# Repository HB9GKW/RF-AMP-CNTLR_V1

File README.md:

# RF-AMP-CNTLR_V1
HB9GKW RF Amplifier Controller

Features:

* Save sequencing of: 
	- Input and output relays with handshake and adjustable delays
	- Amplifier gate enable
	- ALC blanking voltage

* Control of up to 2 power amplifier modules

* Fast analog interlocking:
	- 4x VSWR
	- 2x RF input overload
	- Overcurrent
	- 2x Temperature

* High power MOSFET high side switch with voltage/current sense to disable amplifiers drain supply

* PTT input and adjustable ALC output

* Digital monitoring interface compatible for Raspberry Pi (40 pin header):
	- Amplifier operation and fault states
	- 12 ADC channels (12bit) for voltage, current, 4x forward/reflected, 2x temperature reading

* On-board power supplies (12V, -12V, 5V, 3.3V)

* Can be powered either by mains or external 13.8V supply

* Enhanced RF relay switching speed circuitry compatible for 12V and 24V RF relays

* Radio CAT control, Band and Antenna switching and general purpose interfacing ports for I2C and SPI

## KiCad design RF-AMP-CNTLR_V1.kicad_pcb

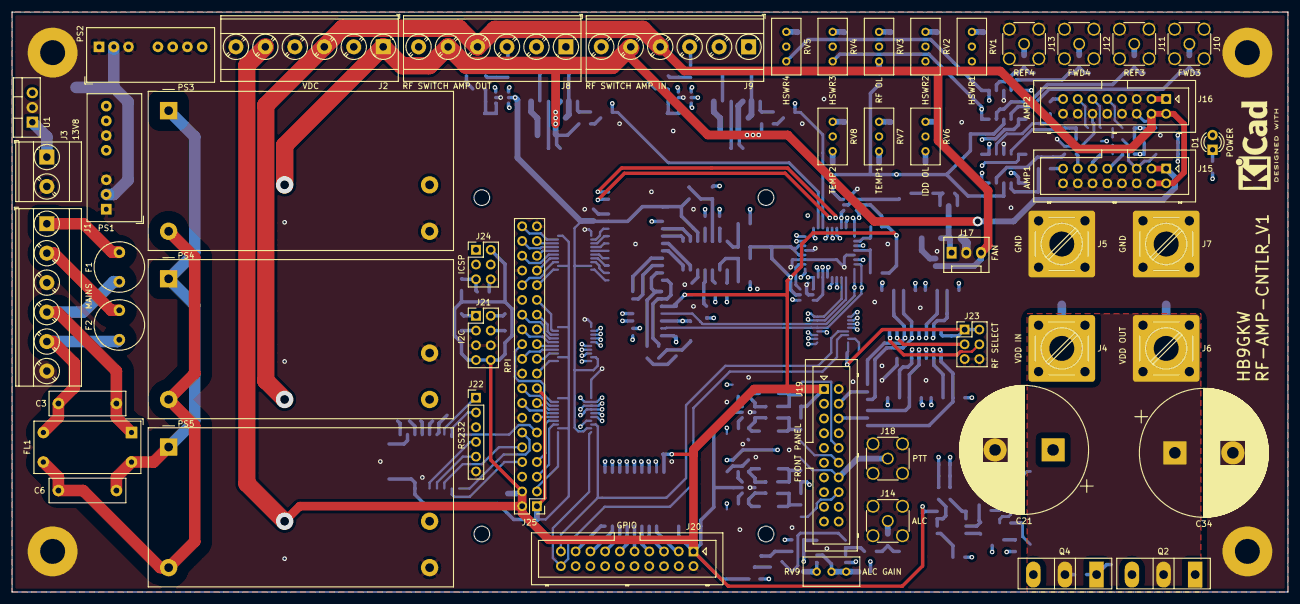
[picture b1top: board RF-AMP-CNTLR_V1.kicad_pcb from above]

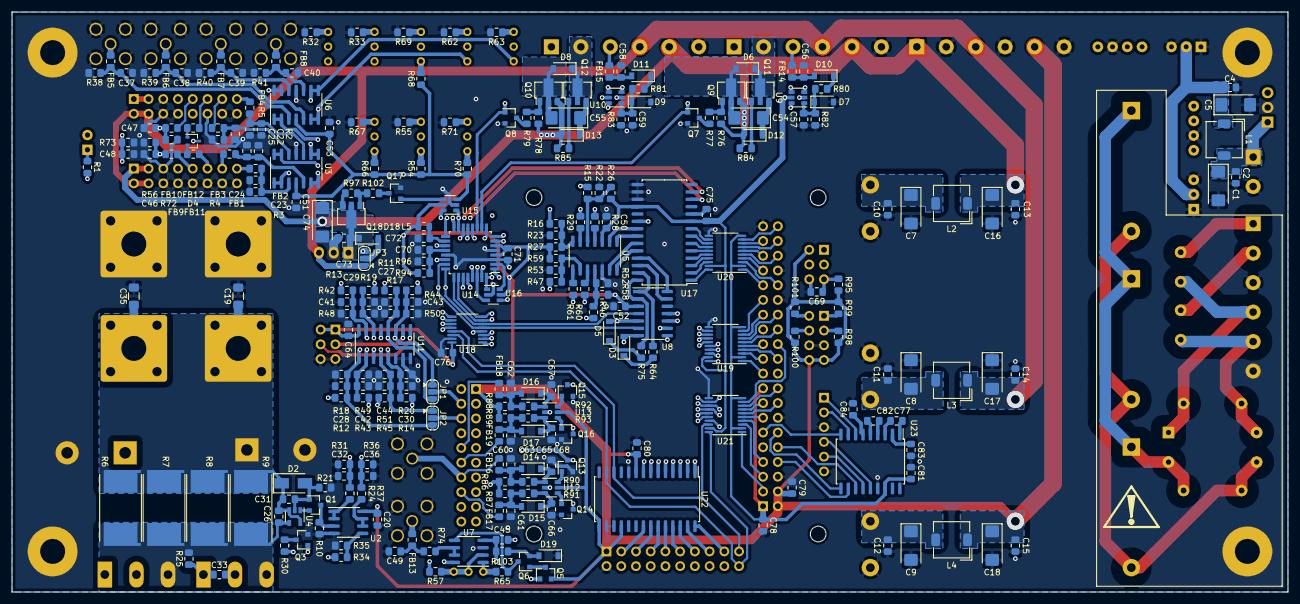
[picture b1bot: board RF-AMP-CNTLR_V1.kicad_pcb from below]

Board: 4 copper layers, 220.0 x 100.0 mm, 316 parts (266 on the bottom side), 252 nets.

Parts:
C1, C5, C7, C8, C9, C16, C17, C18, C74: 47u; CP_EIA-6032-28_Kemet-C
C2, C4, C10, C11, C12, C13, C14, C15, C20, C26, C31, C32, C33, C36, C45, C49, C50, C51, C52, C53, C64, C66, C67, C68, C70, C71, C72, C75, C76, C77, C78, C79, C80, C81, C82, C83, C84: 100n; C_0805_2012Metric_Pad1.15x1.40mm_HandSolder
C3, C6: 68n; C_Rect_L13.0mm_W4.0mm_P10.00mm_FKS3_FKP3_MKS4
C19, C35: 100n; C_1206_3216Metric_Pad1.42x1.75mm_HandSolder
C21, C34: 470u; CP_Radial_D22.0mm_P10.00mm_SnapIn
C22, C23, C24, C25, C37, C38, C39, C40, C48, C60, C61, C62, C63, C69, C73: 1n; C_0805_2012Metric_Pad1.15x1.40mm_HandSolder
C27, C28, C29, C30, C41, C42, C43, C44, C46, C47, C56, C57, C58, C59: 47n; C_0805_2012Metric_Pad1.15x1.40mm_HandSolder
C54, C55: 4u7; CP_EIA-6032-28_Kemet-C
C65: 10n; C_0805_2012Metric_Pad1.15x1.40mm_HandSolder
D1: Power; LED_D3.0mm
D2: Z1SMA33; D_SMA
D3, D5, D10, D11, D14, D15, D16, D17: 1N4148W; D_SOD-123
D4: BAT54CW; SOT-323_SC-70
D6, D8, D12, D13, D18: PMEG6010CEH; D_SOD-123
D7, D9, D19: BZT52C4V7T-7; D_SOD-123
F1, F2: 1AT; Fuse_Littelfuse_372_D8.50mm
FB1, FB2, FB3, FB4, FB5, FB6, FB7, FB8, FB9, FB10, FB11, FB12, FB13, FB14, FB15, FB16, FB17, FB18, FB19: Ferrite_Bead_Small; R_0805_2012Metric_Pad1.15x1.40mm_HandSolder
FL1: EMI_Filter_CommonMode; Choke_Schaffner_RN202-04-8.8x18.2mm
J1: VAC; TerminalBlock_Phoenix_MKDS-3-6-5.08_1x06_P5.08mm_Horizontal
J2: VDC; TerminalBlock_Phoenix_MKDS-3-6-5.08_1x06_P5.08mm_Horizontal
J3: ext_13V8; TerminalBlock_Phoenix_MKDS-3-2-5.08_1x02_P5.08mm_Horizontal
J4: VDD IN; TerminalBlock_MetzConnect_360425_1x01_Horizontal_ScrewM4.0_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
J5: VSS IN; TerminalBlock_MetzConnect_360425_1x01_Horizontal_ScrewM4.0_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
J6: VDD OUT; TerminalBlock_MetzConnect_360425_1x01_Horizontal_ScrewM4.0_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
J7: VSS OUT; TerminalBlock_MetzConnect_360425_1x01_Horizontal_ScrewM4.0_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
J8: RF SWITCH AMP OUT; TerminalBlock_Phoenix_MKDS-3-6-5.08_1x06_P5.08mm_Horizontal
J9: RF SWITCH AMP IN; TerminalBlock_Phoenix_MKDS-3-6-5.08_1x06_P5.08mm_Horizontal
J10: FWD3; SMA_Amphenol_132134_Vertical
J11: REF3; SMA_Amphenol_132134_Vertical
J12: FWD4; SMA_Amphenol_132134_Vertical
J13: REF4; SMA_Amphenol_132134_Vertical
J14: ALC; SMA_Amphenol_132134_Vertical
J15: AMP1; Multicomp_MC9A12-1634_2x08_P2.54mm_Vertical
J16: AMP2; Multicomp_MC9A12-1634_2x08_P2.54mm_Vertical
J17: FAN; FanPinHeader_1x03_P2.54mm_Vertical
J18: PTT; SMA_Amphenol_132134_Vertical
J19: FRONT PANEL; Multicomp_MC9A12-2034_2x10_P2.54mm_Vertical
J20: GPIO; Multicomp_MC9A12-2034_2x10_P2.54mm_Vertical
J21: I2C; PinHeader_2x04_P2.54mm_Vertical
J22: UART; PinHeader_1x06_P2.54mm_Vertical
J23: Conn_02x03_Odd_Even; PinHeader_2x03_P2.54mm_Vertical
J24: ICSP; PinHeader_2x03_P2.54mm_Vertical
J25: Raspberry_Pi_2_3; PinHeader_2x20_P2.54mm_Vertical
JP1, JP2, JP3: SolderJumper_3_Bridged12; SolderJumper-3_P1.3mm_Open_RoundedPad1.0x1.5mm
L1, L2, L3, L4: 10u; L_TDK_SLF6045
L5: 10u; L_0805_2012Metric
PS1: ITQ2412SA; Converter_DCDC_XP_POWER-ITXxxxxSA_THT
PS2: ITQ2405SA; Converter_DCDC_XP_POWER-ITXxxxxSA_THT
PS3, PS4: IRM-20-12; Converter_ACDC_MeanWell_IRM-20-xx_THT
PS5: IRM-20-5; Converter_ACDC_MeanWell_IRM-20-xx_THT
Q1: BC857; SOT-23
Q2, Q4: IXTH140P10T; TO-247-3_Vertical
Q3, Q6, Q7, Q8, Q13, Q14, Q15, Q16, Q17: DTC124E; SOT-23
Q5: DTA124E; SOT-23
Q9, Q10, Q11, Q12, Q18: BCX53; SOT-89-3
R1: 2k2; R_0805_2012Metric_Pad1.15x1.40mm_HandSolder
R2, R3, R4, R5, R38, R39, R40, R41, R56, R72: 100k; R_0805_2012Metric_Pad1.15x1.40mm_HandSolder
R6, R7, R8, R9: 0R015; R_Shunt_Vishay_WSR2_WSR3_KelvinConnection
R10: 68k; R_0805_2012Metric_Pad1.15x1.40mm_HandSolder
R11, R12, R13, R14, R24, R37, R42, R43, R44, R45, R74: 330; R_0805_2012Metric_Pad1.15x1.40mm_HandSolder
R15, R16, R46, R47: 8k2; R_0805_2012Metric_Pad1.15x1.40mm_HandSolder
R17, R18, R19, R20, R25, R31, R34, R36, R48, R49, R50, R51, R57, R65, R82, R83, R84, R85, R86, R87, R88, R89, R90, R91, R92, R93, R95, R98, R99, R100, R101: 10k; R_0805_2012Metric_Pad1.15x1.40mm_HandSolder
R21, R28, R29, R54, R60, R61, R66, R68, R70, R76, R78, R96, R97, R103: 4k7; R_0805_2012Metric_Pad1.15x1.40mm_HandSolder
R22, R23, R52, R53, R55, R67, R69, R71, R80, R81, R94: 1k; R_0805_2012Metric_Pad1.15x1.40mm_HandSolder
R26, R27, R30, R58, R59: 47k; R_0805_2012Metric_Pad1.15x1.40mm_HandSolder
R32, R33, R62, R63, R64, R75: 15k; R_0805_2012Metric_Pad1.15x1.40mm_HandSolder
R35: 680; R_0805_2012Metric_Pad1.15x1.40mm_HandSolder
R73: 470; R_0805_2012Metric_Pad1.15x1.40mm_HandSolder
R77, R79, R102: 110; R_0805_2012Metric_Pad1.15x1.40mm_HandSolder
RV1, RV2, RV3, RV4, RV5, RV6, RV7, RV8, RV9: 20k; Potentiometer_Bourns_3296W_Vertical
U1: L7812; TO-220-3_Vertical
U2, U7: NCS20072D; SOIC-8_3.9x4.9mm_P1.27mm
U3, U6: NCS20074D; SOIC-14_3.9x8.7mm_P1.27mm
U4: INA138; SOT-23-5
U5, U8: LM339; SOIC-14_3.9x8.7mm_P1.27mm
U9, U10: 74LVC2G17; SOT-23-6
U11: CD4052B; SOIC-16_3.9x9.9mm_P1.27mm
U12, U13: 74LVC2G14; SOT-23-6
U14: ATmega8-16AU; TQFP-32_7x7mm_P0.8mm
U15, U16: SN74LVC1G11DBVR; SOT-23-6
U17, U22: MCP23017_SO; SOIC-28W_7.5x17.9mm_P1.27mm
U18: MAX11616; QSOP-16_3.9x4.9mm_P0.635mm
U19, U20, U21: TXS0108EPW; TSSOP-20_4.4x6.5mm_P0.65mm
U23: MAX3232; SOIC-18W_7.5x11.6mm_P1.27mm

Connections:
+3V3: C78.1, C81.1, J25.1, J25.17, U19.2, U19.10, U20.2, U20.10, U21.2, U21.10, U23.16
+5V: C15.1, C18.1, C20.1, C50.1, C51.1, C52.1, C53.1, C64.1, C71.1, C75.1, C76.1, C79.1, C80.1, J2.5, J19.1, J20.1, J21.7, J21.8, J23.1, J23.2, J24.2, J25.2, J25.4, L4.1, L5.2, Q5.2, R26.2, R27.2, R54.1, R58.2, R59.2, R66.1, R68.1, R70.1, R86.1, R87.1, R88.1, R89.1, R94.2, R95.1, R98.2, R99.2, R100.2, R101.2, U2.8, U3.4, U5.3, U6.4, U8.3, U9.5, U10.5, U11.16, U12.5, U13.5, U14.4, U14.6, U15.3, U15.5, U16.5, U17.9, U17.18, U18.16, U19.19, U20.19, U21.19, U22.9, U22.15, U22.18
+12V: C13.1, C16.1, C45.1, C74.1, D1.2, D12.2, D13.2, J2.1, J8.5, J9.5, J15.1, J15.3, J16.1, J16.3, L2.1, Q9.3, Q10.3, Q18.3, R76.2, R78.2, R84.2, R85.2, R97.2, U7.8
-12V: C14.1, C17.2, C45.2, J2.3, J8.4, J9.4, J15.2, J15.4, J16.2, J16.4, J17.3, JP3.1, L3.1, R1.2, R103.2, U7.4
/+5V_: C9.1, C12.1, L4.2, PS2.6, PS5.4
/+12V_: C7.1, C10.1, L2.2, PS3.4, U1.3
/-12V_: C8.2, C11.1, L3.2, PS1.7, PS4.3
/CONTROLLER/DISPLAY: Q16.3, U14.14, U19.13
/CONTROLLER/DISPLAY_: FB19.2, J19.12
/CONTROLLER/DISPLAY_LV: J25.27, U19.8
/CONTROLLER/FAN+: C73.1, D18.1, J17.1, Q18.2
/CONTROLLER/FAULT: J19.19, U14.8, U21.17
/CONTROLLER/FAULT_LV: J25.7, U21.4
/CONTROLLER/GATE_ALC_EN_LV: J25.16, U21.6
/CONTROLLER/GPA0: J20.3, U22.21
/CONTROLLER/GPA1: J20.5, U22.22
/CONTROLLER/GPA2: J20.7, U22.23
/CONTROLLER/GPA3: J20.9, U22.24
/CONTROLLER/GPA4: J20.11, U22.25
/CONTROLLER/GPA5: J20.13, U22.26
/CONTROLLER/GPA6: J20.15, U22.27
/CONTROLLER/GPA7: J20.17, U22.28
/CONTROLLER/GPB0: J20.18, U22.1
/CONTROLLER/GPB1: J20.16, U22.2
/CONTROLLER/GPB2: J20.14, U22.3
/CONTROLLER/GPB3: J20.12, U22.4
/CONTROLLER/GPB4: J20.10, U22.5
/CONTROLLER/GPB5: J20.8, U22.6
/CONTROLLER/GPB6: J20.6, U22.7
/CONTROLLER/GPB7: J20.4, U22.8
/CONTROLLER/HSWR1: U17.1, U20.20
/CONTROLLER/HSWR1_LV: J25.31, U20.1
/CONTROLLER/HSWR2: U17.2, U20.18
/CONTROLLER/HSWR2_LV: J25.32, U20.3
/CONTROLLER/HSWR3: U17.3, U20.17
/CONTROLLER/HSWR3_LV: J25.33, U20.4
/CONTROLLER/HSWR4: U17.4, U20.16
/CONTROLLER/IDD_OL: U17.6, U20.14
/CONTROLLER/IDD_OL_LV: J25.38, U20.7
/CONTROLLER/ILK: U14.32, U16.1, U17.20
/CONTROLLER/ILK_HSWR1: U5.2, U17.21
/CONTROLLER/ILK_HSWR2: U5.1, U17.22
/CONTROLLER/ILK_HSWR3: U5.13, U17.23
/CONTROLLER/ILK_HSWR4: U5.14, U17.24
/CONTROLLER/ILK_IDD_OL: U8.13, U17.26
/CONTROLLER/ILK_RF_OL: U8.14, U17.25
/CONTROLLER/ILK_TEMP1: R64.2, U8.1, U17.27
/CONTROLLER/ILK_TEMP2: R75.2, U8.2, U17.28
/CONTROLLER/MISO_RF_INHIBIT: J24.1, U14.16, U19.18
/CONTROLLER/MISO_RF_INHIBIT_LV: J25.21, U19.3
/CONTROLLER/MOSI_FAN: J24.4, U14.15, U15.1, U19.20
/CONTROLLER/MOSI_FAN_LV: J25.19, U19.1
/CONTROLLER/ON_AIR: J19.17, U14.7, U21.16
/CONTROLLER/ON_AIR_LV: J25.13, U21.5
/CONTROLLER/OPR: Q14.3, U14.12, U19.15
/CONTROLLER/OPR_: FB17.2, J19.16
/CONTROLLER/OPR_LV: J25.26, U19.6
/CONTROLLER/PTT: Q13.3, U14.1, U19.14
/CONTROLLER/PTT_: FB16.2, J18.1, J19.14
/CONTROLLER/PTT_LV: J25.28, U19.7
/CONTROLLER/RESET_ILK: Q15.3, U14.13, U19.12
/CONTROLLER/RESET_ILK_: FB18.2, J19.10
/CONTROLLER/RESET_ILK_LV: J25.29, U19.9
/CONTROLLER/RESET_ISP: C69.1, J24.5, R95.2, U14.29, U15.6, U19.17
/CONTROLLER/RESET_ISP_LV: J25.22, U19.4
/CONTROLLER/RF_OL: U17.5, U20.15
/CONTROLLER/RF_OL_LV: J25.35, U20.6
/CONTROLLER/RF_SW1_ON_LV: J25.18, U21.8
/CONTROLLER/RF_SW2_ON_LV: J25.15, U21.7
/CONTROLLER/RXD0: J25.10, U23.12
/CONTROLLER/RXD0_RS: J22.5, U23.13
/CONTROLLER/RXD1: J25.11, U23.9
/CONTROLLER/RXD1_RS: J22.2, U23.8
/CONTROLLER/SCK_SOFT_ILK: J24.3, U14.17, U19.16
/CONTROLLER/SCK_SOFT_ILK_LV: J25.23, U19.5
/CONTROLLER/SCL_PI_HV: J20.19, J21.4, R100.1, U18.13, U21.18, U22.12
/CONTROLLER/SCL_PI_LV: J25.5, U21.3
/CONTROLLER/SDA_PI_HV: J20.20, J21.2, R101.1, U18.14, U21.20, U22.13
/CONTROLLER/SDA_PI_LV: J25.3, U21.1
/CONTROLLER/SELA: J23.3, U11.10
/CONTROLLER/SELB: J23.4, U11.9
/CONTROLLER/TEMP: U17.8, U20.12
/CONTROLLER/TEMP_LV: J25.40, U20.9
/CONTROLLER/TXD0: J25.8, U23.11
/CONTROLLER/TXD0_RS: J22.4, U23.14
/CONTROLLER/TXD1: J25.12, U23.10
/CONTROLLER/TXD1_RS: J22.1, U23.7
/CONTROLLER/UNBAL_LV: J25.36, U20.5
/CONTROLLER/VDD_EN_LV: J25.24, U21.9
/CONTROLLER/VDD_LIM: U17.7, U20.13
/CONTROLLER/VDD_LIM_LV: J25.37, U20.8
/FRONTEND/ALC: FB13.1, J14.1
/FRONTEND/FWD1: FB1.2, J15.13
/FRONTEND/FWD2: FB3.2, J16.13
/FRONTEND/FWD3: FB5.2, J10.1
/FRONTEND/FWD4: FB7.2, J12.1
/FRONTEND/REF1: FB2.2, J15.15
/FRONTEND/REF2: FB4.2, J16.15
/FRONTEND/REF3: FB6.2, J11.1
/FRONTEND/REF4: FB8.2, J13.1
/FRONTEND/RF_OL1: FB11.2, J15.11
/FRONTEND/RF_OL2: FB12.2, J16.11
/FRONTEND/RF_SW1: D6.1, J8.2, Q11.2
/FRONTEND/RF_SW1_EN_: J8.1, U9.4
/FRONTEND/RF_SW1_ON_: FB14.1, J8.3
/FRONTEND/RF_SW2: D8.1, J9.2, Q12.2
/FRONTEND/RF_SW2_EN_: J9.1, U10.4
/FRONTEND/RF_SW2_ON_: FB15.1, J9.3
/FRONTEND/TEMP1: FB9.2, J15.9
/FRONTEND/TEMP2: FB10.2, J16.9
/FRONTEND/VDD_IN: C19.1, C21.1, C26.2, C31.1, D2.1, J4.1, R6.2, R7.2, R8.2, R9.2, U4.3, U4.5
/FRONTEND/VDD_OUT: C33.2, C34.1, C35.1, J6.1, Q2.2, Q4.2, R34.1
/FWD1_MON: C27.1, JP1.3, R11.2, R17.2, U11.12, U18.9
/FWD2_MON: C29.1, R13.2, R19.2, U11.14, U18.11
/FWD3_MON: C41.1, R42.2, R48.2, U11.15, U18.4
/FWD4_MON: C43.1, JP1.1, R44.2, R50.2, U11.11, U18.2
/GATE_ALC_EN: J15.7, J16.7, J19.15, Q5.1, U16.4, U21.15
/IDD_MON: C32.1, J19.3, R24.1, R31.2, U8.10, U14.26, U18.8
/REF1_MON: C28.1, JP2.3, R12.2, R18.2, U11.1, U18.10
/REF2_MON: C30.1, R14.2, R20.2, U11.5, U18.12
/REF3_MON: C42.1, R43.2, R49.2, U11.2, U18.3
/REF4_MON: C44.1, JP2.1, R45.2, R51.2, U11.4, U18.1
/RF_SW1_EN: Q7.1, U9.3, U14.10
/RF_SW1_ON: J19.11, U9.6, U14.30, U16.3, U21.13
/RF_SW2_EN: Q8.1, U10.3, U14.11
/RF_SW2_ON: J19.13, U10.6, U14.31, U21.14
/SCL: J19.20, J21.3, R98.1, U14.28, U17.12
/SDA: J19.18, J21.1, R99.1, U14.27, U17.13
/TEMP1_MON: C46.1, FB9.1, J19.7, R56.1, U8.6, U14.23, U18.5
/TEMP2_MON: C47.1, FB10.1, J19.9, R72.1, U8.4, U14.24, U18.6
/VDD_EN: J19.8, Q3.1, U14.9, U21.12
/VDD_MON: C36.1, J19.5, R36.2, R37.2, U14.25, U18.7
Earth: C1.2, C2.2, C4.2, C5.2, C7.2, C8.1, C9.2, C10.2, C11.2, C12.2, C13.2, C14.2, C15.2, C16.2, C17.1, C18.2, C19.2, C20.2, C21.2, C22.2, C23.2, C24.2, C25.2, C27.2, C28.2, C29.2, C30.2, C32.2, C34.2, C35.2, C36.2, C37.2, C38.2, C39.2, C40.2, C41.2, C42.2, C43.2, C44.2, C46.2, C47.2, C48.2, C49.2, C50.2, C51.2, C52.2, C53.2, C56.2, C57.2, C58.2, C59.2, C60.2, C61.2, C62.2, C63.2, C64.2, C65.2, C66.2, C67.2, C68.2, C69.2, C70.2, C71.2, C72.2, C73.2, C74.2, C75.2, C76.2, C78.2, C79.2, C80.2, C81.2, C83.2, C84.2, D7.2, D9.2, D19.1, J1.3, J1.6, J2.2, J2.4, J2.6, J3.2, J5.1, J7.1, J8.6, J9.6, J10.2, J11.2, J12.2, J13.2, J14.2, J15.5, J15.6, J15.8, J15.10, J15.12, J15.14, J15.16, J16.5, J16.6, J16.8, J16.10, J16.12, J16.14, J16.16, J17.2, J18.2, J19.2, J20.2, J21.5, J21.6, J22.3, J22.6, J23.5, J23.6, J24.6, J25.6, J25.9, J25.14, J25.20, J25.25, J25.30, J25.34, J25.39, JP3.3, PS1.1, PS1.3, PS1.6, PS2.1, PS2.3, PS2.7, PS3.3, PS4.4, PS5.3, Q3.2, Q7.2, Q8.2, Q13.2, Q14.2, Q15.2, Q16.2, Q17.2, R2.2, R3.2, R4.2, R5.2, R10.2, R17.1, R18.1, R19.1, R20.1, R21.2, R22.2, R23.2, R31.1, R32.2, R33.2, R35.2, R36.1, R38.2, R39.2, R40.2, R41.2, R48.1, R49.1, R50.1, R51.1, R52.2, R53.2, R55.2, R56.2, R62.2, R63.2, R67.2, R69.2, R71.2, R72.2, R73.2, R82.2, R83.2, R96.2, U1.2, U2.4, U3.11, U5.12, U6.11, U7.3, U8.12, U9.2, U10.2, U11.6, U11.7, U11.8, U12.2, U13.2, U14.3, U14.5, U14.21, U15.2, U16.2, U17.10, U17.15, U17.16, U17.17, U18.15, U19.11, U20.11, U21.11, U22.10, U22.16, U22.17, U23.15
FWD: J19.4, JP1.2, R57.2
unnamed: C1.1, C2.1, J3.1, L1.2, U1.1
unnamed: C3.1, F1.1, FL1.1, J1.4
unnamed: C3.2, F2.1, FL1.3, J1.5
unnamed: C4.1, C5.1, L1.1, PS1.2, PS2.2
unnamed: C6.1, FL1.2, PS3.1, PS4.1, PS5.1
unnamed: C6.2, FL1.4, PS3.2, PS4.2, PS5.2
unnamed: C22.1, FB1.1, R2.1, U3.5
unnamed: C23.1, FB2.1, R3.1, U3.3
unnamed: C24.1, FB3.1, R4.1, U3.12
unnamed: C25.1, FB4.1, R5.1, U3.10
unnamed: C26.1, Q2.3, Q4.3, R6.1, R7.1, R8.1, R9.1, R25.2, U4.4
unnamed: C31.2, D2.2, Q1.1, R21.1, U4.2
unnamed: C33.1, Q2.1, Q4.1, R25.1, R30.2
unnamed: C37.1, FB5.1, R38.1, U6.3
unnamed: C38.1, FB6.1, R39.1, U6.5
unnamed: C39.1, FB7.1, R40.1, U6.12
unnamed: C40.1, FB8.1, R41.1, U6.10
unnamed: C48.1, D4.3, R73.1, U8.8
unnamed: C49.1, FB13.2, R74.1
unnamed: C54.1, D12.1, Q11.3
unnamed: C54.2, D6.2, Q9.2
unnamed: C55.1, D13.1, Q12.3
unnamed: C55.2, D8.2, Q10.2
unnamed: C56.1, D10.2, FB14.2
unnamed: C57.1, D7.1, R80.2, R82.1, U9.1
unnamed: C58.1, D11.2, FB15.2
unnamed: C59.1, D9.1, R81.2, R83.1, U10.1
unnamed: C60.1, D14.2, FB16.1, R86.2, R90.2
unnamed: C61.1, D15.2, FB17.1, R87.2, R91.2
unnamed: C62.1, D16.2, FB18.1, R88.2, R92.2
unnamed: C63.1, D17.2, FB19.1, R89.2, R93.2
unnamed: C65.1, D14.1, R90.1, U12.1
unnamed: C66.1, D15.1, R91.1, U12.3
unnamed: C67.1, D16.1, R92.1, U13.1
unnamed: C68.1, D17.1, R93.1, U13.3
unnamed: C70.1, R94.1, R96.1, U14.20
unnamed: C72.1, L5.1, U14.18
unnamed: C77.1, U23.1
unnamed: C77.2, U23.3
unnamed: C82.1, U23.4
unnamed: C82.2, U23.5
unnamed: C83.1, U23.2
unnamed: C84.1, U23.6
unnamed: D1.1, R1.1
unnamed: D3.1, R64.1
unnamed: D3.2, RV7.2, U8.7
unnamed: D4.1, FB12.1
unnamed: D4.2, FB11.1
unnamed: D5.1, R75.1
unnamed: D5.2, RV8.2, U8.5
unnamed: D10.1, R80.1
unnamed: D11.1, R81.1
unnamed: D18.2, JP3.2
unnamed: D19.2, Q6.2, R103.1
unnamed: F1.2, J1.1
unnamed: F2.2, J1.2
unnamed: Q1.2, U4.1
unnamed: Q1.3, R10.1, U2.3
unnamed: Q3.3, R30.1
unnamed: Q5.3, Q6.1
unnamed: Q6.3, R65.1, U7.5
unnamed: Q7.3, R77.1
unnamed: Q8.3, R79.1
unnamed: Q9.1, R76.1, R77.2
unnamed: Q10.1, R78.1, R79.2
unnamed: Q11.1, R84.1
unnamed: Q12.1, R85.1
unnamed: Q13.1, U12.6
unnamed: Q14.1, U12.4
unnamed: Q15.1, U13.6
unnamed: Q16.1, U13.4
unnamed: Q17.1, U15.4
unnamed: Q17.3, R102.1
unnamed: Q18.1, R97.1, R102.2
unnamed: R11.1, R15.2, U3.6, U3.7
unnamed: R12.1, RV1.1, U3.1, U3.2
unnamed: R13.1, R16.2, U3.13, U3.14
unnamed: R14.1, RV2.1, U3.8, U3.9
unnamed: R15.1, R22.1, R26.1, U5.5
unnamed: R16.1, R23.1, R27.1, U5.7
unnamed: R24.2, U2.1, U2.2
unnamed: R28.1, RV1.2
unnamed: R28.2, U5.4
unnamed: R29.1, RV2.2
unnamed: R29.2, U5.6
unnamed: R32.1, RV1.3
unnamed: R33.1, RV2.3
unnamed: R34.2, R35.1, U2.5
unnamed: R37.1, U2.6, U2.7
unnamed: R42.1, R46.2, U6.1, U6.2
unnamed: R43.1, RV4.1, U6.6, U6.7
unnamed: R44.1, R47.2, U6.13, U6.14
unnamed: R45.1, RV5.1, U6.8, U6.9
unnamed: R46.1, R52.1, R58.1, U5.11
unnamed: R47.1, R53.1, R59.1, U5.9
unnamed: R54.2, RV7.1
unnamed: R55.1, RV7.3
unnamed: R57.1, RV9.2, RV9.3, U7.2
unnamed: R60.1, RV4.2
unnamed: R60.2, U5.10
unnamed: R61.1, RV5.2
unnamed: R61.2, U5.8
unnamed: R62.1, RV4.3
unnamed: R63.1, RV5.3
unnamed: R65.2, RV9.1, U7.1
unnamed: R66.2, RV6.1
unnamed: R67.1, RV6.3
unnamed: R68.2, RV3.1
unnamed: R69.1, RV3.3
unnamed: R70.2, RV8.1
unnamed: R71.1, RV8.3
unnamed: R74.2, U7.6, U7.7
unnamed: RV3.2, U8.9
unnamed: RV6.2, U8.11
unnamed: U11.3, U14.22
unnamed: U11.13, U14.19
unnamed: U14.2, U16.6
REF: J19.6, JP2.2

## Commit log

2019-11-12 blabla
2019-11-12 remove file
2019-11-12 added file
2019-11-24 readme update
2019-12-01 Review 1
2020-01-11 Review 2
2020-01-13 changing gerber format
2020-01-19 Review
2020-02-03 prototype bug fixes
2020-02-03 BOM entry fixes
2020-02-09 bug fixes
2020-07-17 new Version with AVR Controller
2020-08-24 forgot to update
2020-08-24 remove unused
2020-08-29 bug fix ITQ ON/OFF
2020-08-30 bug fix level shifter U19-U21 VCCA VCCB swap
2020-10-25 ALC latch-up fix
